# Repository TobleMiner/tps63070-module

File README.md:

2 - 16 V step-up/down module
============================

Simple 2 - 16 V step-up/down DC-DC module, footprint-compatible to MP1584EN

Optional headers for regulator control and power good signals.

# PCB

## Top

## Bottom

# Library

This design comes with reference KiCAD module schematic symbols, footprints
and 3d models. Copy

* models
* tps63070-module.lib
* tps63070-module.pretty

to the root of your project and include the schematic symbols from
`tps63070-module.lib` as well as the footprints from `tps63070-module.pretty`.

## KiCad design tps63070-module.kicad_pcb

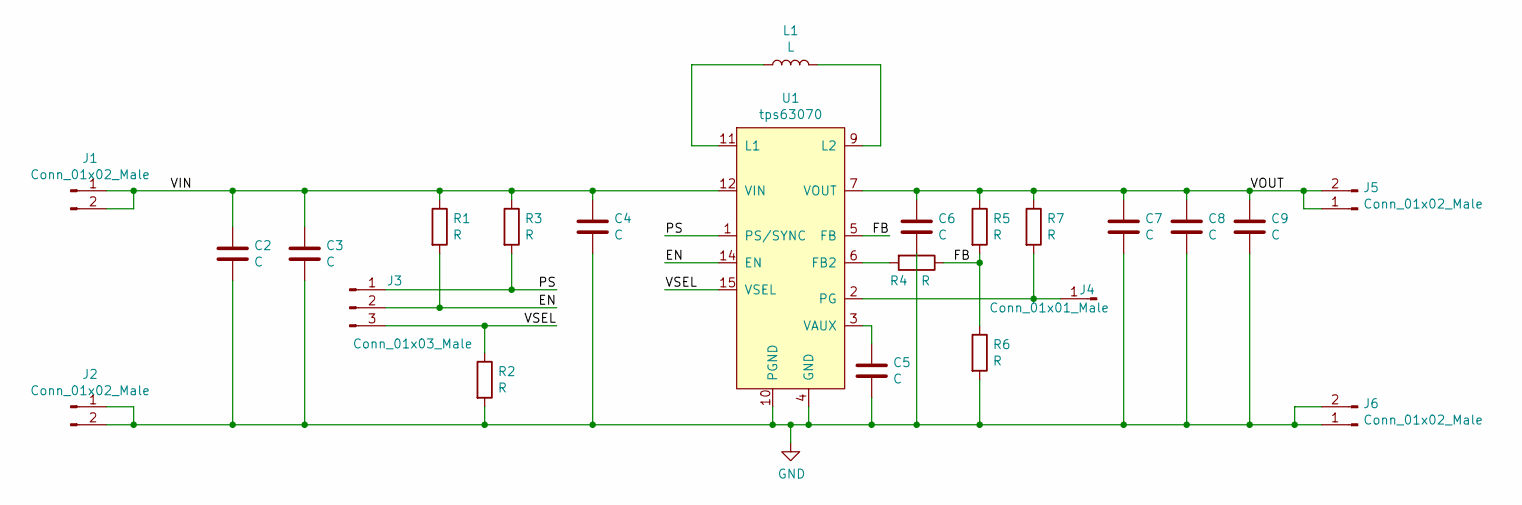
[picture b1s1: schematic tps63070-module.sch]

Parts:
C2, C3, C5, C7, C8, C9: C; C_0805_2012Metric_Pad1.15x1.40mm_HandSolder
C4, C6: C; C_0603_1608Metric_Pad1.05x0.95mm_HandSolder
J1, J2, J5, J6: Conn_01x02_Male; PinHeader_1x02_P2.54mm_Vertical
J3: Conn_01x03_Male; PinHeader_1x03_P2.54mm_Vertical
J4: Conn_01x01_Male; PinHeader_1x01_P2.54mm_Vertical
L1: L; L_Coilcraft_XxL4020
R1, R2, R3, R4, R5, R6, R7: R; R_0805_2012Metric_Pad1.15x1.40mm_HandSolder
U1: tps63070; VQFN-HR-15

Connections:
/EN: J3.2, R1.2, U1.14 (EN)
/FB: R4.1, R5.2, R6.1, U1.5 (FB)
/PS: J3.1, R3.2, U1.1 (PS/SYNC)
/VIN: C2.1, C3.1, C4.1, J1.1, J1.2, R1.1, R3.1, U1.12 (VIN)
/VOUT: C6.1, C7.1, C8.1, C9.1, J5.1, J5.2, R5.1, R7.1, U1.7 (VOUT)
/VSEL: J3.3, R2.1, U1.15 (VSEL)
GND: C2.2, C3.2, C4.2, C5.1, C6.2, C7.2, C8.2, C9.2, J2.1, J2.2, J6.1, J6.2, R2.2, R6.2, U1.4 (GND), U1.10 (PGND)
unnamed: C5.2, U1.3 (VAUX)
unnamed: J4.1, R7.2, U1.2 (PG)
unnamed: L1.1, U1.11 (L1)
unnamed: L1.2, U1.9 (L2)
unnamed: R4.2, U1.6 (FB2)

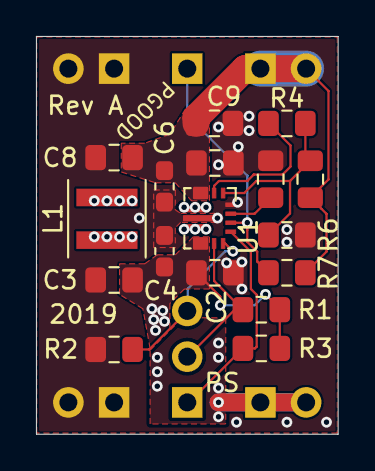
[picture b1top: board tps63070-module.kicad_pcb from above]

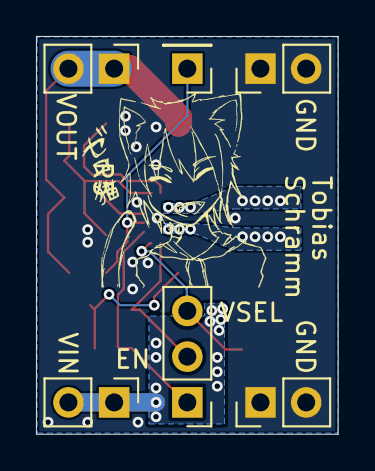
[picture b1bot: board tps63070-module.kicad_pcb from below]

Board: 2 copper layers, 16.8 x 22.1 mm, 23 parts (6 on the bottom side), 12 nets.

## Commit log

2019-06-16 Add schematic
2019-06-16 Place components
2019-06-17 Do some routing
2019-06-17 Add groundplanes
2019-06-19 Route board
2019-06-19 Add PCB art
2019-06-19 Ignore cache files
2019-06-19 Connect VOUT on top Cu layer, too
2019-06-19 Add more silkscreen designators
2019-06-24 Add 3d models
2019-06-24 Ignore autosave files
2019-06-24 Add module footprints and 3d models
2019-06-24 Reposition designator C4
2019-06-24 Add README
2019-06-24 Add instructions on using KiCad models
2019-06-25 Fix module footprints
    Pins were flipped horizontally
2019-06-25 Optimize PCB footprint
    * Move front exclusion zone to include only pin headers
    * Enlarge front silkscreen outline to cover whole area of module
2019-06-25 Panelize
2019-06-25 Fix typo
    It's a TPS63070 not a TSP63070
2019-06-25 Add panel render
2019-06-25 Add art to PCB panel
